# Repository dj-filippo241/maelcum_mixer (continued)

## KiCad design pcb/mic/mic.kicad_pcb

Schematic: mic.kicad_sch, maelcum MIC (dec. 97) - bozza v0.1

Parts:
C1, C2: 220u 35V; CP_Radial_D8.0mm_P3.50mm
C3: 47u 10V; CP_Radial_D5.0mm_P2.00mm
C4, C8: 10u 35V; CP_Radial_D5.0mm_P2.00mm
C5, C9: 47u 35V; CP_Radial_D6.3mm_P2.50mm
C6, C10: 470u 25V; CP_Radial_D8.0mm_P3.50mm
C7, C11: 100u 25V; CP_Radial_D6.3mm_P2.50mm
C12, C13: 1u 50V; C_1206_3216Metric
C14, C15, C39: 1u 25V; C_1206_3216Metric
C16, C17, C19, C20: 4u7 25V; C_1206_3216Metric
C18, C21: 10u 25V; C_1206_3216Metric
C22, C23: 100p C0G; C_0805_2012Metric
C24, C25, C26, C27, C33, C34, C35, C36, C37, C38, C40, C45, C46, C47, C48, C52, C53, C54, C56, C57, C58, C59, C62, C63, C64, C65, C66, C67: 100n; C_0805_2012Metric
C28, C29: 220n C0G; C_1210_3225Metric
C30: 22p C0G; C_0805_2012Metric
C31, C49: 47p C0G; C_0805_2012Metric
C32: 100n C0G; C_1206_3216Metric
C41, C42: 180n C0G; C_1206_3216Metric
C43, C44: 10n C0G; C_1206_3216Metric
C50, C51: 1u C0G; C_1206_3216Metric
C55: 220n C0G; C_1206_3216Metric
C60, C61: 10p C0G; C_0805_2012Metric
D1, D3, D5, D6, D7, D8, D9, D10, D11, D12, D13, D14, D15: 1N4148W; D_SOD-123
D2, D4: S1G; D_SMA
FB1, FB2, FB3, FB4, FB5, FB6, FB7: ferrite 600R; L_1206_3216Metric
H1, H2: CHASSIS; MountingHole_3.2mm_M3_Pad
J1: C96 maschio; DIN41612_C_3x32_Male_Horizontal_THT
J2: 2x12 cavo piatto; PinHeader_2x12_P2.54mm_Vertical
J3: XLR (cavo); PinHeader_1x03_P2.54mm_Vertical
Q1, Q2: 2N7002; SOT-23
Q40: BD139; TO-126-3_Vertical
Q41: BD140; TO-126-3_Vertical
R1, R4: 120 1%; R_0805_2012Metric
R2, R5: 1k74 1%; R_0805_2012Metric
R3, R6, R27, R37, R38, R58, R87: 1k; R_0805_2012Metric
R7, R8: 150k 0.1%; R_0805_2012Metric
R9, R11: 10 1%; R_0805_2012Metric
R10, R12: 47k 1%; R_0805_2012Metric
R13: 2k32 1%; R_0805_2012Metric
R14, R15: 499 0.1%; R_0805_2012Metric
R16: 32.4 0.1%; R_0805_2012Metric
R17, R18, R19, R20, R69, R71: 1k 0.1%; R_0805_2012Metric
R21: 8k45 0.1%; R_0805_2012Metric
R22: 16k9 0.1%; R_0805_2012Metric
R23: 332 0.1%; R_0805_2012Metric
R24: 5k36 0.1%; R_0805_2012Metric
R25, R43, R44, R53, R54, R56, R57, R62, R64, R65, R66, R89, R90, R91, R92, R93, R94, R95, R96: 10k 0.1%; R_0805_2012Metric
R26: 2k49 0.1%; R_0805_2012Metric
R28: 3M; R_0805_2012Metric
R29: 133k 0.1%; R_0805_2012Metric
R30: 7k68 0.1%; R_0805_2012Metric
R31: 6k65 0.1%; R_0805_2012Metric
R32: 1k1 0.1%; R_0805_2012Metric
R33, R34, R36, R67, R68, R86: 10k; R_0805_2012Metric
R35: 750k; R_0805_2012Metric
R39, R40: 324 0.1%; R_0805_2012Metric
R41: 4k75 0.1%; R_0805_2012Metric
R42: 2k26 0.1%; R_0805_2012Metric
R45, R46, R47: 49k9 0.1%; R_0805_2012Metric
R48, R52, R55, R76, R77, R78, R79, R80, R81: 20k 0.1%; R_0805_2012Metric
R49: 5k1; R_0805_2012Metric
R50: 150k; R_0805_2012Metric
R51: 51; R_0805_2012Metric
R59: 1M; R_0805_2012Metric
R60: 100; R_0805_2012Metric
R61: 16k 0.1%; R_0805_2012Metric
R63: 169k 0.1%; R_0805_2012Metric
R70: 2k 0.1%; R_0805_2012Metric
R72, R74: 4k99 0.1%; R_0805_2012Metric
R73, R75: 274 0.1%; R_0805_2012Metric
R82, R83, R84, R85: 2k2; R_0805_2012Metric
R88: 100k; R_0805_2012Metric
RV1: 50k; Potentiometer_Bourns_3266W_Vertical
U1, U2, U8, U11: OPA1612AIDR; SOIC-8_3.9x4.9mm_P1.27mm
U3, U4, U6, U7, U10: OPA1654AIDR; SOIC-14_3.9x8.7mm_P1.27mm
U5: V2181L; SOIC-8_3.9x4.9mm_P1.27mm
U9: ADG1434YRUZ; TSSOP-20_4.4x6.5mm_P0.65mm
U30: LM339DR; SOIC-14_3.9x8.7mm_P1.27mm
U40: LM317; TO-220-3_Vertical
U41: LM337; TO-220-3_Vertical
U42: 78L15; SOT-89-3
U43: 79L15; SOT-89-3
U44: LT3045EMSE; MSOP-12-1EP_3x4.039mm_P0.65mm_EP1.651x2.845mm
U45: LT3094EMSE; MSOP-12-1EP_3x4.039mm_P0.65mm_EP1.651x2.845mm

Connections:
+5V: FB5.1, J1.a21, J1.a22
+5VF: C3.1, C40.1, FB5.2, J2.20, R33.1, R35.1, R36.1, R86.1, R88.2, U30.3 (VCC)
+15LN: C18.1, C24.1, C26.1, C33.1, C47.1, C52.1, C56.1, C58.1, D5.1 (K), D7.1 (K), R29.1, R63.1, RV1.1, U1.8 (V+), U2.8 (V+), U3.4 (V+), U5.7 (V+), U6.4 (V+), U7.4 (V+), U11.8 (V+), U44.10 (OUTS), U44.11 (OUT), U44.12 (OUT)
+15SW: C14.1, C64.1, U9.16 (VDD), U42.1 (OUT)
+18V: C7.1, C17.1, C45.1, C62.1, C66.1, Q40.1 (E), U4.4 (V+), U8.8 (V+), U10.4 (V+), U44.1 (IN), U44.2 (IN), U44.3 (IN), U44.4 (EN/UV), U44.7 (PGFB)
-15LN: C21.2, C25.2, C27.2, C34.2, C48.2, C53.2, C57.2, C59.2, D6.2 (A), D8.2 (A), R49.2, RV1.3, U1.4 (V-), U2.4 (V-), U3.11 (V-), U6.11 (V-), U7.11 (V-), U11.4 (V-), U45.10 (OUTS), U45.11 (OUT), U45.12 (OUT)
-15SW: C15.2, C65.2, U9.5 (VSS), U43.3 (VO)
-18V: C11.2, C20.2, C46.2, C63.2, C67.2, Q41.1 (E), U4.11 (V-), U8.4 (V-), U10.11 (V-), U45.1 (IN), U45.2 (IN), U45.3 (EN/UV), U45.5 (PGFB), U45.13 (IN)
ADJ+: C4.1, D1.2 (A), R1.2, R2.1, U40.1 (ADJ)
ADJ-: C8.2, D3.1 (K), R4.2, R5.1, U41.1 (ADJ)
AGND: C1.2, C2.1, C4.2, C5.2, C6.2, C7.2, C8.1, C9.1, C10.1, C11.1, C12.2, C13.1, C14.2, C15.1, C16.2, C17.2, C18.2, C19.1, C20.1, C21.1, C24.2, C25.1, C26.2, C27.1, C32.2, C33.2, C34.1, C35.2, C36.2, C37.2, C45.2, C46.1, C47.2, C48.1, C50.2, C51.2, C52.2, C53.1, C54.2, C55.2, C56.2, C57.1, C58.2, C59.1, C62.2, C63.1, C64.2, C65.1, C66.2, C67.1, J1.a13, J1.a14, J1.a15, J1.a16, J1.a17, J1.a18, J1.a19, J1.a20, J1.b3, J1.b6, J1.b9, J1.b12, J1.b15, J1.b18, J1.b21, J1.b24, J1.b27, J1.b30, J2.1, J2.5, J2.9, J2.13, J2.19, R2.2, R5.2, R7.2, R8.2, R10.2, R12.2, R20.2, R22.2, R26.2, R28.2, R32.2, R42.2, R51.2, R59.2, R64.2, R68.2, R71.2, R73.2, R75.2, U2.5 (+), U3.5 (+), U4.3 (+), U4.10 (+), U4.12 (+), U5.2 (EC+), U5.6 (GND), U6.3 (+), U6.5 (+), U6.10 (+), U7.10 (+), U8.3 (+), U8.5 (+), U9.4 (S1B), U9.6 (GND), U9.7 (S2B), U9.14 (S3B), U9.17 (S4B), U11.5 (+), U42.2 (GND), U43.1 (GND), U44.6 (ILIM), U44.9 (GND), U44.13 (GND), U45.6 (ILIM), U45.9 (GND)
BASE+: C6.1, Q40.3 (B), R3.2
BASE-: C10.2, Q41.3 (B), R6.2
CF: C23.1, FB7.2, R11.1
CHASSIS: C22.2, C23.2, H1.1, H2.1, J1.a25, J1.a26, J3.1
CTRL_GND: C3.2, C38.2, C39.2, C40.2, J1.a23, J1.a24, J1.c16, J1.c20, J1.c24, J1.c28, J2.24, Q2.2 (S), R34.2, U30.12 (GND)
D1A: D9.2 (A), R27.2
DN: R17.2, R18.1, U2.2 (-)
DOUT: C31.1, R27.1, U3.8
DP: R19.2, R20.1, U2.3 (+)
DRV_L: C60.2, R77.2, R78.1, U8.1
DRV_R: C61.2, R80.2, R81.1, U8.7
DSUB: R62.2, R65.1, U7.7
ECF: R72.1, R73.1, U11.2 (-)
ECM: R74.2, R75.1, U5.3 (EC-)
ECO: R72.2, R74.1, U11.1
ECS: R69.2, R70.2, R71.1, U11.3 (+)
F1: R14.2, R16.1, U1.2 (-)
F2: R15.2, R16.2, U1.6 (-)
GFD: Q1.3 (D), R38.2
GINV: C30.1, J2.3, U3.6 (-)
GLOBAL_MUTE: J1.c9, R87.1
GP1: J2.2, R23.2
GP2: J2.4, R24.1
HF: C22.1, FB6.2, R9.1
HN: D15.2 (A), R65.2, R66.1, U7.9 (-)
HO: D14.2 (A), D15.1 (K), U7.8
HOLD: C31.2, C32.1, D9.1 (K), R28.1, U3.9 (-), U3.12 (+)
HP: R21.2, R23.1, U3.1, U3.2 (-)
HW: D11.2 (A), R54.2, R56.1
IC: D7.2 (A), D8.1 (K), R11.2, R12.1, R13.2, U1.5 (+)
IH: D5.2 (A), D6.1 (K), R9.2, R10.1, R13.1, U1.3 (+)
INJ1: R89.1, R90.1, U10.1, U10.2 (-)
INJ2: R91.1, R92.1, U10.6 (-), U10.7
INJ3: R93.1, R94.1, U10.8, U10.9 (-)
INJ4: R95.1, R96.1, U10.13 (-), U10.14
K1: C28.2, C29.1, R21.1
K2: C29.2, R22.1, U3.3 (+)
KG: Q1.2 (S), U30.13 (4OUT)
KR: D10.2 (A), R37.2, U30.14 (3OUT)
LIM: D14.1 (K), R66.2, R69.1
LKG: J2.21, R38.1
LKR: J2.22, R37.1
LQ: D10.1 (K), Q1.1 (G), R36.2, U30.2 (2OUT)
LT: C39.1, R35.2, U30.1 (1OUT), U30.5 (2IN+)
MET: U3.13 (-), U3.14, U30.6 (1IN-), U30.8 (3IN-), U30.10 (4IN-)
MG: R25.2, R26.1, U3.10 (+)
MRC: C55.1, R67.2, R68.1, U7.12 (+)
MSUM6_L: J1.b1, R78.2
MSUM6_R: J1.b2, R81.2
MUTE_CV: R70.1, U7.13 (-), U7.14
MUTE_G: Q2.1 (G), R87.2, R88.1
MUTE_SW: J2.23, R67.1
NA: C41.1, J2.6, R39.2
NB: C41.2, C42.1, J2.7, U4.2 (-)
NC: C42.2, J2.8, R40.1
NDR_L: C60.1, R76.2, R77.1, U8.2 (-)
NDR_R: C61.1, R79.2, R80.1, U8.6 (-)
NHA: C43.2, C44.1, R41.1
NHB: C44.2, R42.1, U4.5 (+)
NIV: C49.1, R52.1, U5.8 (OUT), U6.2 (-)
NSH: R45.2, R46.2, R47.1, U4.13 (-)
NU2: U2.6 (-), U2.7
NU11: U11.6 (-), U11.7
NVH: R43.2, R44.1, U4.9 (-)
O1: R14.1, R17.1, U1.1
O2: R15.1, R19.1, U1.7
PK: C50.1, R58.2, R59.1, R60.1
POST: C49.2, J2.14, R52.2, R53.1, R55.1, R76.1, R79.1, U6.1
POSTEQ: R47.2, R48.1, U4.14
PRE: C30.2, R24.2, R25.1, R39.1, U3.7
RAN: D12.1 (K), R53.2, R54.1, U6.6 (-)
RAO: D11.1 (K), D12.2 (A), U6.7
RAW+22: FB3.1, J1.a5, J1.a6
RAW+27: FB1.1, J1.a1, J1.a2
RAW-22: FB4.1, J1.a7, J1.a8
RAW-27: FB2.1, J1.a3, J1.a4
RBN: R55.2, R56.2, R57.1, U6.9 (-)
RECT: R57.2, U6.8, U6.12 (+)
S1: C28.1, R18.2, U2.1
S1_OUT_L: J1.b4, R89.2
S1_OUT_R: J1.b5, R90.2
S2_OUT_L: J1.b7, R91.2
S2_OUT_R: J1.b8, R92.2
S3_OUT_L: J1.b10, R93.2
S3_OUT_R: J1.b11, R94.2
S4_OUT_L: J1.b13, R95.2
S4_OUT_R: J1.b14, R96.2
SDK: D13.1 (K), R58.1, U6.13 (-)
SDO: D13.2 (A), U6.14
SETN: C19.2, R8.1, U45.8 (SET)
SETP: C16.1, R7.1, U44.8 (SET)
SIN1: R82.2, U9.2 (S1A), U9.3 (D1), U10.3 (+)
SIN2: R83.2, U9.8 (D2), U9.9 (S2A), U10.5 (+)
SIN3: R84.2, U9.12 (S3A), U9.13 (D3), U10.10 (+)
SIN4: R85.2, U9.18 (D4), U9.19 (S4A), U10.12 (+)
SM: C51.1, R60.2, U7.3 (+)
SMB: R61.1, U7.1, U7.2 (-)
SMUTE_N: Q2.3 (D), R86.2, U9.1 (IN1), U9.10 (IN2), U9.11 (IN3), U9.20 (IN4)
SUBN: R61.2, R62.1, U7.6 (-)
SUBP: C54.1, R63.2, R64.1, U7.5 (+)
SW1: J2.15, R82.1
SW2: J2.16, R83.1
SW3: J2.17, R84.1
SW4: J2.18, R85.1
SWSYM: R50.1, RV1.2
SYM: R50.2, R51.1, U5.4 (SYM)
V22F+: C12.1, FB3.2, U42.3 (IN)
V22F-: C13.2, FB4.2, U43.2 (VI)
V27F+: C1.1, D2.1 (K), FB1.2, U40.3 (VI)
V27F-: C2.2, D4.2 (A), FB2.2, U41.2 (VI)
VEE: R49.1, U5.5 (V-)
VG: C37.1, R31.2, R32.1, U30.11 (4IN+)
VHN: J2.10, R44.2, U4.8
VHP: J2.12, R41.2, R43.1, U4.6 (-), U4.7
VIN: R48.2, U5.1 (IN)
VLO: C43.1, R40.2, R45.1, U4.1
VR: C35.1, R29.2, R30.1, U30.7 (1IN+)
VREG+: C5.1, D1.1 (K), D2.2 (A), Q40.2 (C), R1.1, R3.1, U40.2 (VO)
VREG-: C9.2, D3.2 (A), D4.1 (K), Q41.2 (C), R4.1, R6.1, U41.3 (VO)
VTL: C38.1, R33.2, R34.1, U30.4 (2IN-)
VY: C36.1, R30.2, R31.1, U30.9 (3IN+)
WPH: J2.11, R46.1
XCOLD: FB7.1, J3.3
XHOT: FB6.1, J3.2

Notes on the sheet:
BACKPLANE C96 (classe MIC/GEN, MSUM6)
ALIM: +18V (LM317 + BD139)
ALIM: -18V (LM337 + BD140)
ALIM: +15SW (78L15)
ALIM: -15SW (79L15)
ALIM: +5VF
ALIM: +15LN (LT3045)
ALIM: -15LN (LT3094)
INGRESSO XLR: RFI, clamp, carico 2,32k, bias 2x47k (mic-pre.inc)
INA +30,05 dB e differenziale unity (OPA1612)
PASSA-ALTO 60 Hz, STADIO 2 (0...+30 dB), DETECTOR del LED (OPA1654)
LED tricolore (LM339)
EQ2 (+-18)
VCA del MUTE e del limiter (dec. 111, 145; sim/mic/mic-limiter.cir)
DRIVER MSUM6 L/R (invertenti, todo 227)
MANDATE S1-S4 (pot sul cavo, mute globale, iniezione)
CAVO SCHEDA COMANDI (J2)

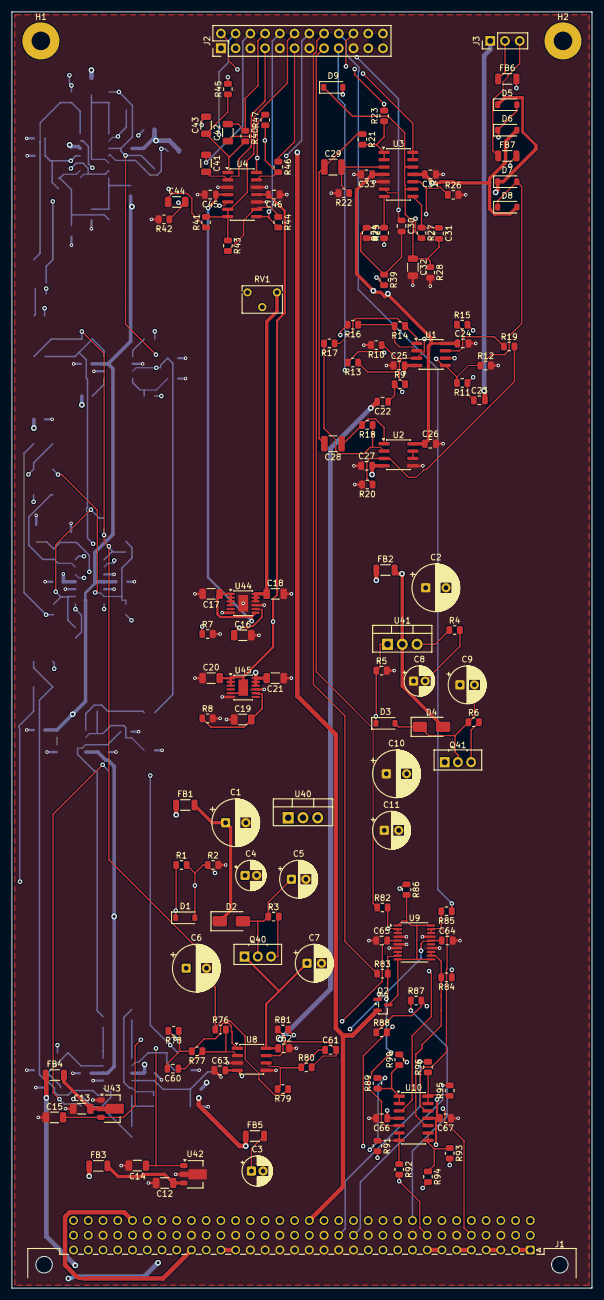
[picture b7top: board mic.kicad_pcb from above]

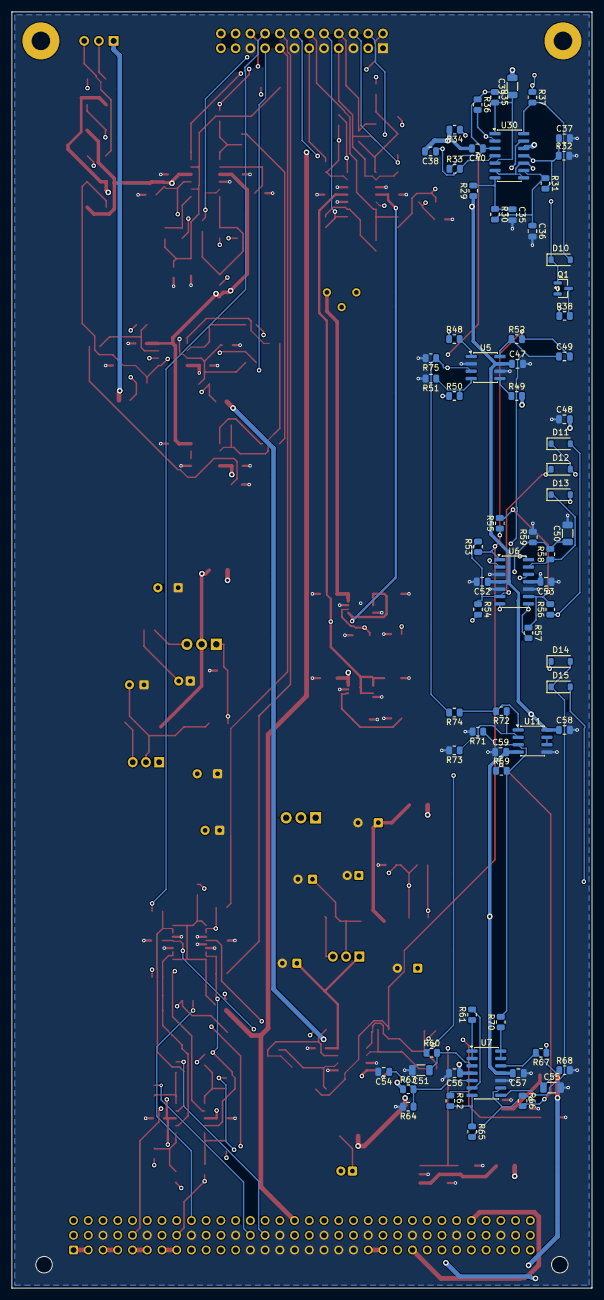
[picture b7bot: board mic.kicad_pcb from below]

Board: 4 copper layers, 100.0 x 220.0 mm, 213 parts (69 on the bottom side), 135 nets.

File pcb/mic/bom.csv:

quantita;valore;impronta;riferimenti;nota
2;220u 35V;CP_Radial_D8.0mm_P3.50mm;C1 C2;
2;1u 50V;C_1206_3216Metric;C12 C13;
3;1u 25V;C_1206_3216Metric;C14 C15 C39;
1;4u7 25V;C_1206_3216Metric;C16;rumore del riferimento (datasheet: 4,7 uF)
3;4u7 25V;C_1206_3216Metric;C17 C19 C20;
2;10u 25V;C_1206_3216Metric;C18 C21;
2;100p C0G;C_0805_2012Metric;C22 C23;RFI verso il telaio
28;100n;C_0805_2012Metric;C24 C25 C26 C27 C33 C34 C35 C36 C37 C38 C40 C45 C46 C47 C48 C52 C53 C54 C56 C57 C58 C59 C62 C63 C64 C65 C66 C67;
2;220n C0G;C_1210_3225Metric;C28 C29;
1;47u 10V;CP_Radial_D5.0mm_P2.00mm;C3;
1;22p C0G;C_0805_2012Metric;C30;
2;47p C0G;C_0805_2012Metric;C31 C49;
1;100n C0G;C_1206_3216Metric;C32;hold: niente altro sul nodo (sim/meter)
2;10u 35V;CP_Radial_D5.0mm_P2.00mm;C4 C8;
2;180n C0G;C_1206_3216Metric;C41 C42;
2;10n C0G;C_1206_3216Metric;C43 C44;
2;47u 35V;CP_Radial_D6.3mm_P2.50mm;C5 C9;
1;1u C0G;C_1206_3216Metric;C50;Ch: C0G o film
1;1u C0G;C_1206_3216Metric;C51;Cs: lisciatura 0,1 ms
1;220n C0G;C_1206_3216Metric;C55;rampa 1,1 ms (dec. 111)
2;470u 25V;CP_Radial_D8.0mm_P3.50mm;C6 C10;
2;10p C0G;C_0805_2012Metric;C60 C61;NOTA: Cf come i ricevitori a massa virtuale
2;100u 25V;CP_Radial_D6.3mm_P2.50mm;C7 C11;
1;1N4148W;D_SOD-123;D1;scarica Cadj
1;1N4148W;D_SOD-123;D10;rosso acceso durante il latch
1;1N4148W;D_SOD-123;D13;diodo del superdiodo
1;S1G;D_SMA;D2;protezione inversa
8;1N4148W;D_SOD-123;D3 D6 D8 D9 D11 D12 D14 D15;
1;S1G;D_SMA;D4;
2;1N4148W;D_SOD-123;D5 D7;NOTA: clamp 1N4148W al posto del BAV199 (pinout non verificato)
7;ferrite 600R;L_1206_3216Metric;FB1 FB2 FB3 FB4 FB5 FB6 FB7;
1;C96 maschio;DIN41612_C_3x32_Male_Horizontal_THT;J1;DIN 41612 C 3x32, angolo retto
1;2x12 cavo piatto;PinHeader_2x12_P2.54mm_Vertical;J2;cavo piatto corto (<= 10 cm) verso la scheda comandi dietro il pannello (dec. 133)
1;XLR (cavo);PinHeader_1x03_P2.54mm_Vertical;J3;NOTA: cavo verso l'XLR femmina; pin 1 a CHASSIS al connettore (grounding §4)
1;2N7002;SOT-23;Q1;spegne il verde durante il latch del rosso
1;2N7002;SOT-23;Q2;GLOBAL_MUTE alto = muto
1;BD139;TO-126-3_Vertical;Q40;
1;BD140;TO-126-3_Vertical;Q41;
2;120 1%;R_0805_2012Metric;R1 R4;
2;47k 1%;R_0805_2012Metric;R10 R12;bias di modo comune (CMRR 74 dB)
1;2k32 1%;R_0805_2012Metric;R13;Zin differenziale 2,26 kOhm
2;499 0.1%;R_0805_2012Metric;R14 R15;
1;32.4 0.1%;R_0805_2012Metric;R16;Rg: G1 = 1 + 998/32,4 = 31,8
1;1k 0.1%;R_0805_2012Metric;R17;caldo sull'ingresso -: il differenziale inverte (todo 227)
3;1k 0.1%;R_0805_2012Metric;R18 R19 R20;
1;1k74 1%;R_0805_2012Metric;R2;E96 1,74k = 19,4 V (fx-send NOTE punto 16)
1;8k45 0.1%;R_0805_2012Metric;R21;
1;16k9 0.1%;R_0805_2012Metric;R22;R_fb = R_gnd/2: Butterworth
1;332 0.1%;R_0805_2012Metric;R23;
1;5k36 0.1%;R_0805_2012Metric;R24;
17;10k 0.1%;R_0805_2012Metric;R25 R43 R44 R53 R54 R56 R57 R64 R65 R89 R90 R91 R92 R93 R94 R95 R96;
1;2k49 0.1%;R_0805_2012Metric;R26;
1;3M;R_0805_2012Metric;R28;release 0,3 s (dec. 81)
1;133k 0.1%;R_0805_2012Metric;R29;
1;1k;R_0805_2012Metric;R3;NOTA: cap-moltiplicatore come il FX-SEND (~50 mA)
1;7k68 0.1%;R_0805_2012Metric;R30;
1;6k65 0.1%;R_0805_2012Metric;R31;
1;1k1 0.1%;R_0805_2012Metric;R32;
4;10k;R_0805_2012Metric;R33 R34 R36 R68;
1;750k;R_0805_2012Metric;R35;latch del rosso: 0,69 x 750k x 1u = 0,52 s
1;1k;R_0805_2012Metric;R37;~2,8 mA nel rosso (LED alta efficienza, metering §1)
1;1k;R_0805_2012Metric;R38;~2,8 mA nel verde
2;324 0.1%;R_0805_2012Metric;R39 R40;
1;4k75 0.1%;R_0805_2012Metric;R41;NOTA: mic-mono §5.1 dice 4,7k/2,25k (~5 kHz); backend.inc 5,23k/2,5k
1;2k26 0.1%;R_0805_2012Metric;R42;E96 di 2,25k
3;49k9 0.1%;R_0805_2012Metric;R45 R46 R47;
7;20k 0.1%;R_0805_2012Metric;R48 R52 R55 R76 R77 R79 R80;
1;5k1;R_0805_2012Metric;R49;valore del datasheet a -15 V (master: 6,19k a -18 V)
1;1k74 1%;R_0805_2012Metric;R5;
1;150k;R_0805_2012Metric;R50;
1;51;R_0805_2012Metric;R51;
1;1k;R_0805_2012Metric;R58;attacco 1 ms
1;1M;R_0805_2012Metric;R59;rilascio 1 s (variante 2)
3;1k;R_0805_2012Metric;R6 R27 R87;
1;100;R_0805_2012Metric;R60;
1;16k 0.1%;R_0805_2012Metric;R61;NOTA: inseguitore su SM, così il sottrattore non carica Ch
1;10k 0.1%;R_0805_2012Metric;R62;G = 10k/16k = 0,625
1;169k 0.1%;R_0805_2012Metric;R63;SUBP = 0,838 V = VTH x 10/26: VTH 2,179 V
1;10k 0.1%;R_0805_2012Metric;R66;Rf: a riposo LIM a massa virtuale (11k con Ra)
1;10k;R_0805_2012Metric;R67;NOTA: tasto a ritenuta fra +5VF e MUTE_SW, come il MONO del master
1;1k 0.1%;R_0805_2012Metric;R69;Ra
2;150k 0.1%;R_0805_2012Metric;R7 R8;
1;2k 0.1%;R_0805_2012Metric;R70;Rb: MUTE 2,5 V -> +0,79 V sulla rete; al pin 0,77 V = -126 dB
1;1k 0.1%;R_0805_2012Metric;R71;Rc
1;4k99 0.1%;R_0805_2012Metric;R72;stadio del limite x19,21 (todo 288)
2;274 0.1%;R_0805_2012Metric;R73 R75;
1;4k99 0.1%;R_0805_2012Metric;R74;partitore 1/19,21: op-amp al rail = 0,80 V al pin
2;20k 0.1%;R_0805_2012Metric;R78 R81;R di somma lato sorgente (dec. 97)
4;2k2;R_0805_2012Metric;R82 R83 R84 R85;
1;10k;R_0805_2012Metric;R86;IN alto = suona (VIH 2,0 V)
1;100k;R_0805_2012Metric;R88;senza master il modulo resta muto (fail-safe, fx-send NOTE 5)
2;10 1%;R_0805_2012Metric;R9 R11;limita la corrente dei clamp
1;50k;Potentiometer_Bourns_3266W_Vertical;RV1;trim di simmetria (vca-trim §3.1)
1;OPA1612AIDR;SOIC-8_3.9x4.9mm_P1.27mm;U1;coppia INA
1;OPA1654AIDR;SOIC-14_3.9x8.7mm_P1.27mm;U10;buffer d'iniezione, non invertenti
1;OPA1612AIDR;SOIC-8_3.9x4.9mm_P1.27mm;U11;stadio del limite del pin EC- (todo 288); seconda sezione libera, inseguitore a massa
1;OPA1612AIDR;SOIC-8_3.9x4.9mm_P1.27mm;U2;differenziale; seconda sezione libera, inseguitore a massa
1;OPA1654AIDR;SOIC-14_3.9x8.7mm_P1.27mm;U3;passa-alto, stadio 2 (pot GAIN 5k sul cavo: GP1-GINV-GP2), superdiodo e buffer del LED
1;LM339DR;SOIC-14_3.9x8.7mm_P1.27mm;U30;NOTA: GND a CTRL_GND (correnti dei LED fuori da AGND); ingressi riferiti ad AGND
1;OPA1654AIDR;SOIC-14_3.9x8.7mm_P1.27mm;U4;EQ2: LOW, HIGH follower, HIGH invertente, HIGH somma
1;LM317;TO-220-3_Vertical;U40;
1;LM337;TO-220-3_Vertical;U41;
1;78L15;SOT-89-3;U42;
1;79L15;SOT-89-3;U43;
1;LT3045EMSE;MSOP-12-1EP_3x4.039mm_P0.65mm_EP1.651x2.845mm;U44;EN/UV a IN; ILIM a massa; PG libero; PGFB a IN (come master-segnale.py)
1;LT3094EMSE;MSOP-12-1EP_3x4.039mm_P0.65mm_EP1.651x2.845mm;U45;EN/UV a IN; PG libero; PGFB a IN; ILIM a massa; VIOC libero
1;V2181L;SOIC-8_3.9x4.9mm_P1.27mm;U5;
1;OPA1654AIDR;SOIC-14_3.9x8.7mm_P1.27mm;U6;I/V del VCA, raddrizzatore A e B, superdiodo
1;OPA1654AIDR;SOIC-14_3.9x8.7mm_P1.27mm;U7;inseguitore di SM, sottrattore, mezza onda, inseguitore del MUTE
1;OPA1612AIDR;SOIC-8_3.9x4.9mm_P1.27mm;U8;driver MSUM invertenti (F2)
1;ADG1434YRUZ;TSSOP-20_4.4x6.5mm_P0.65mm;U9;mute globale delle mandate (dec. 94b): D e SxA sul nodo, SxB a massa

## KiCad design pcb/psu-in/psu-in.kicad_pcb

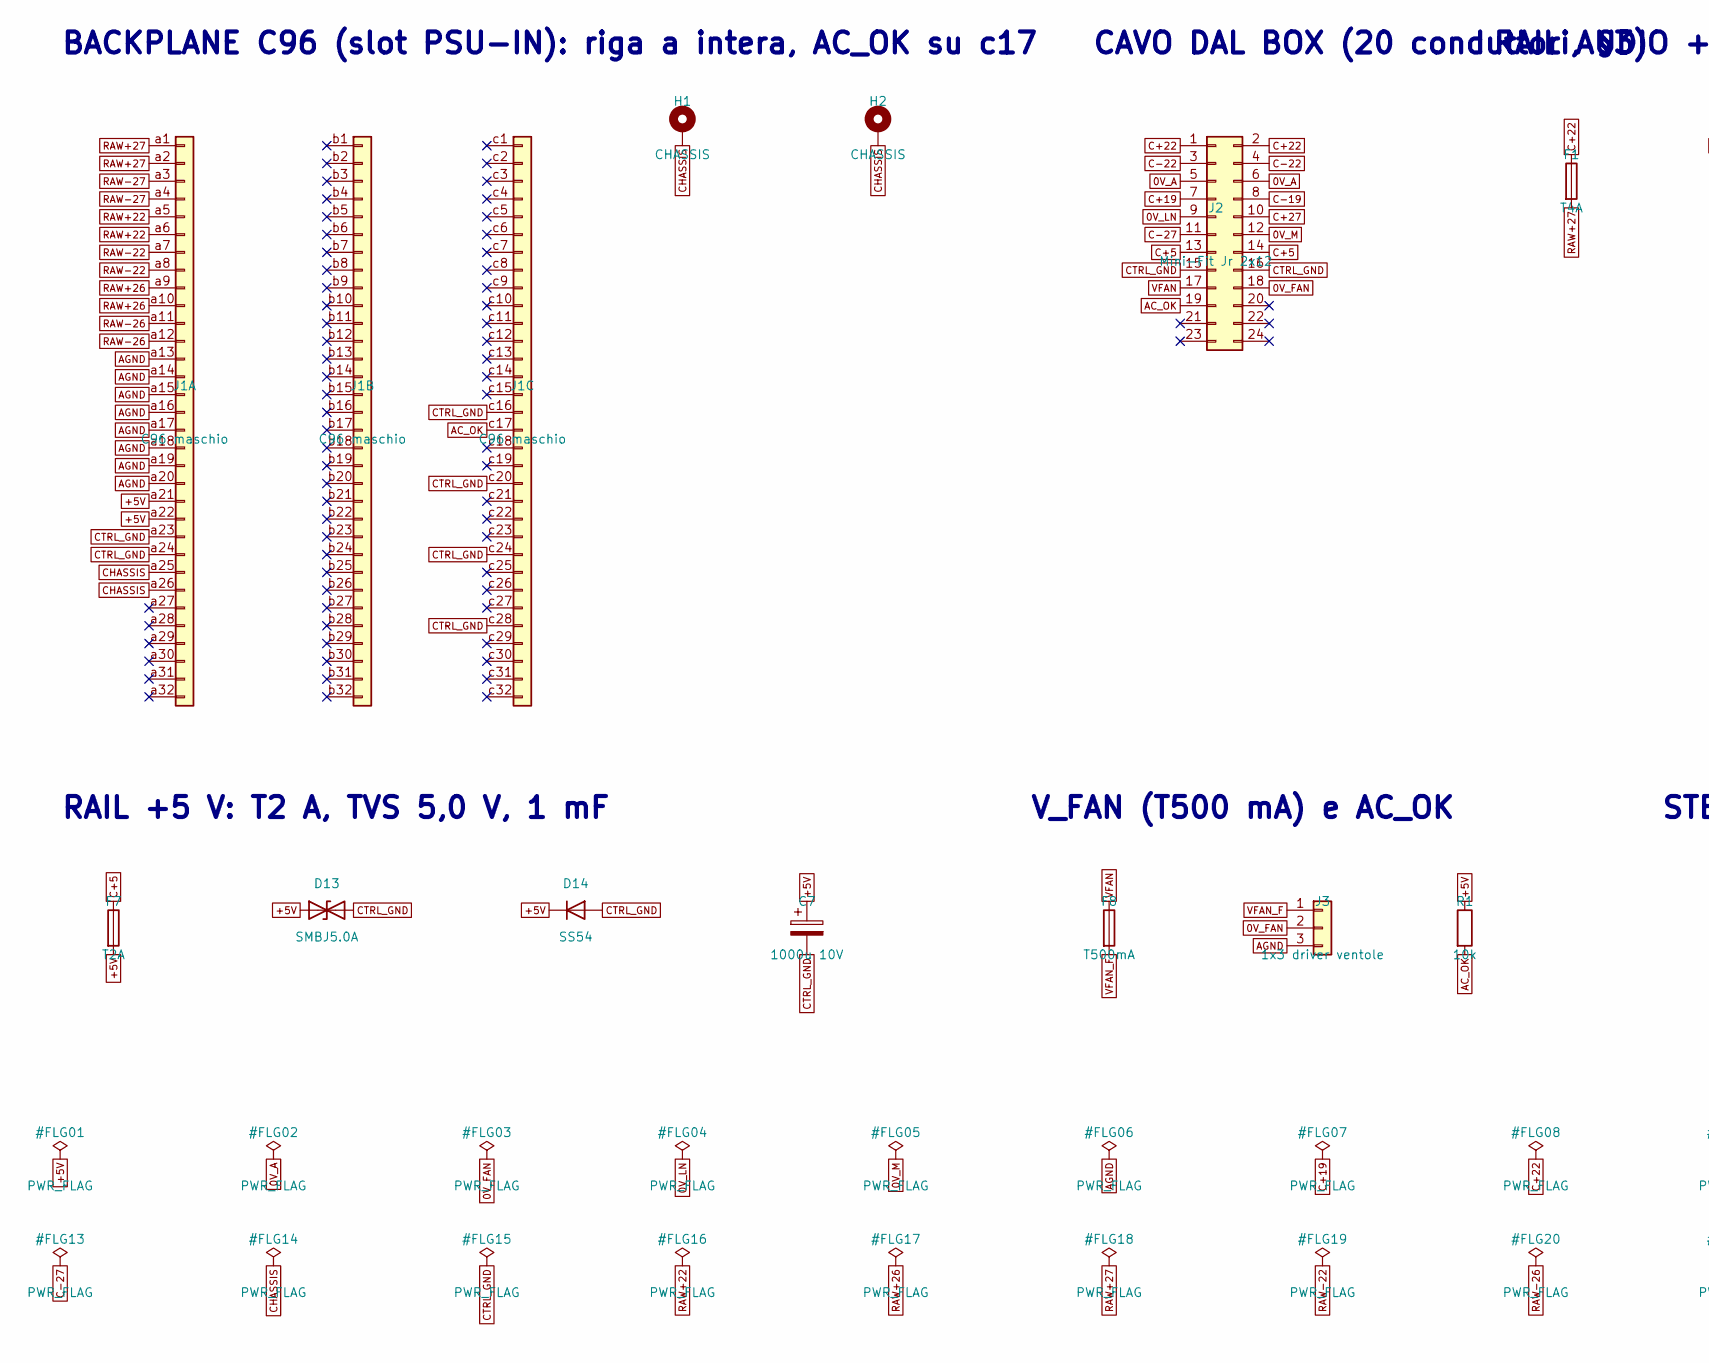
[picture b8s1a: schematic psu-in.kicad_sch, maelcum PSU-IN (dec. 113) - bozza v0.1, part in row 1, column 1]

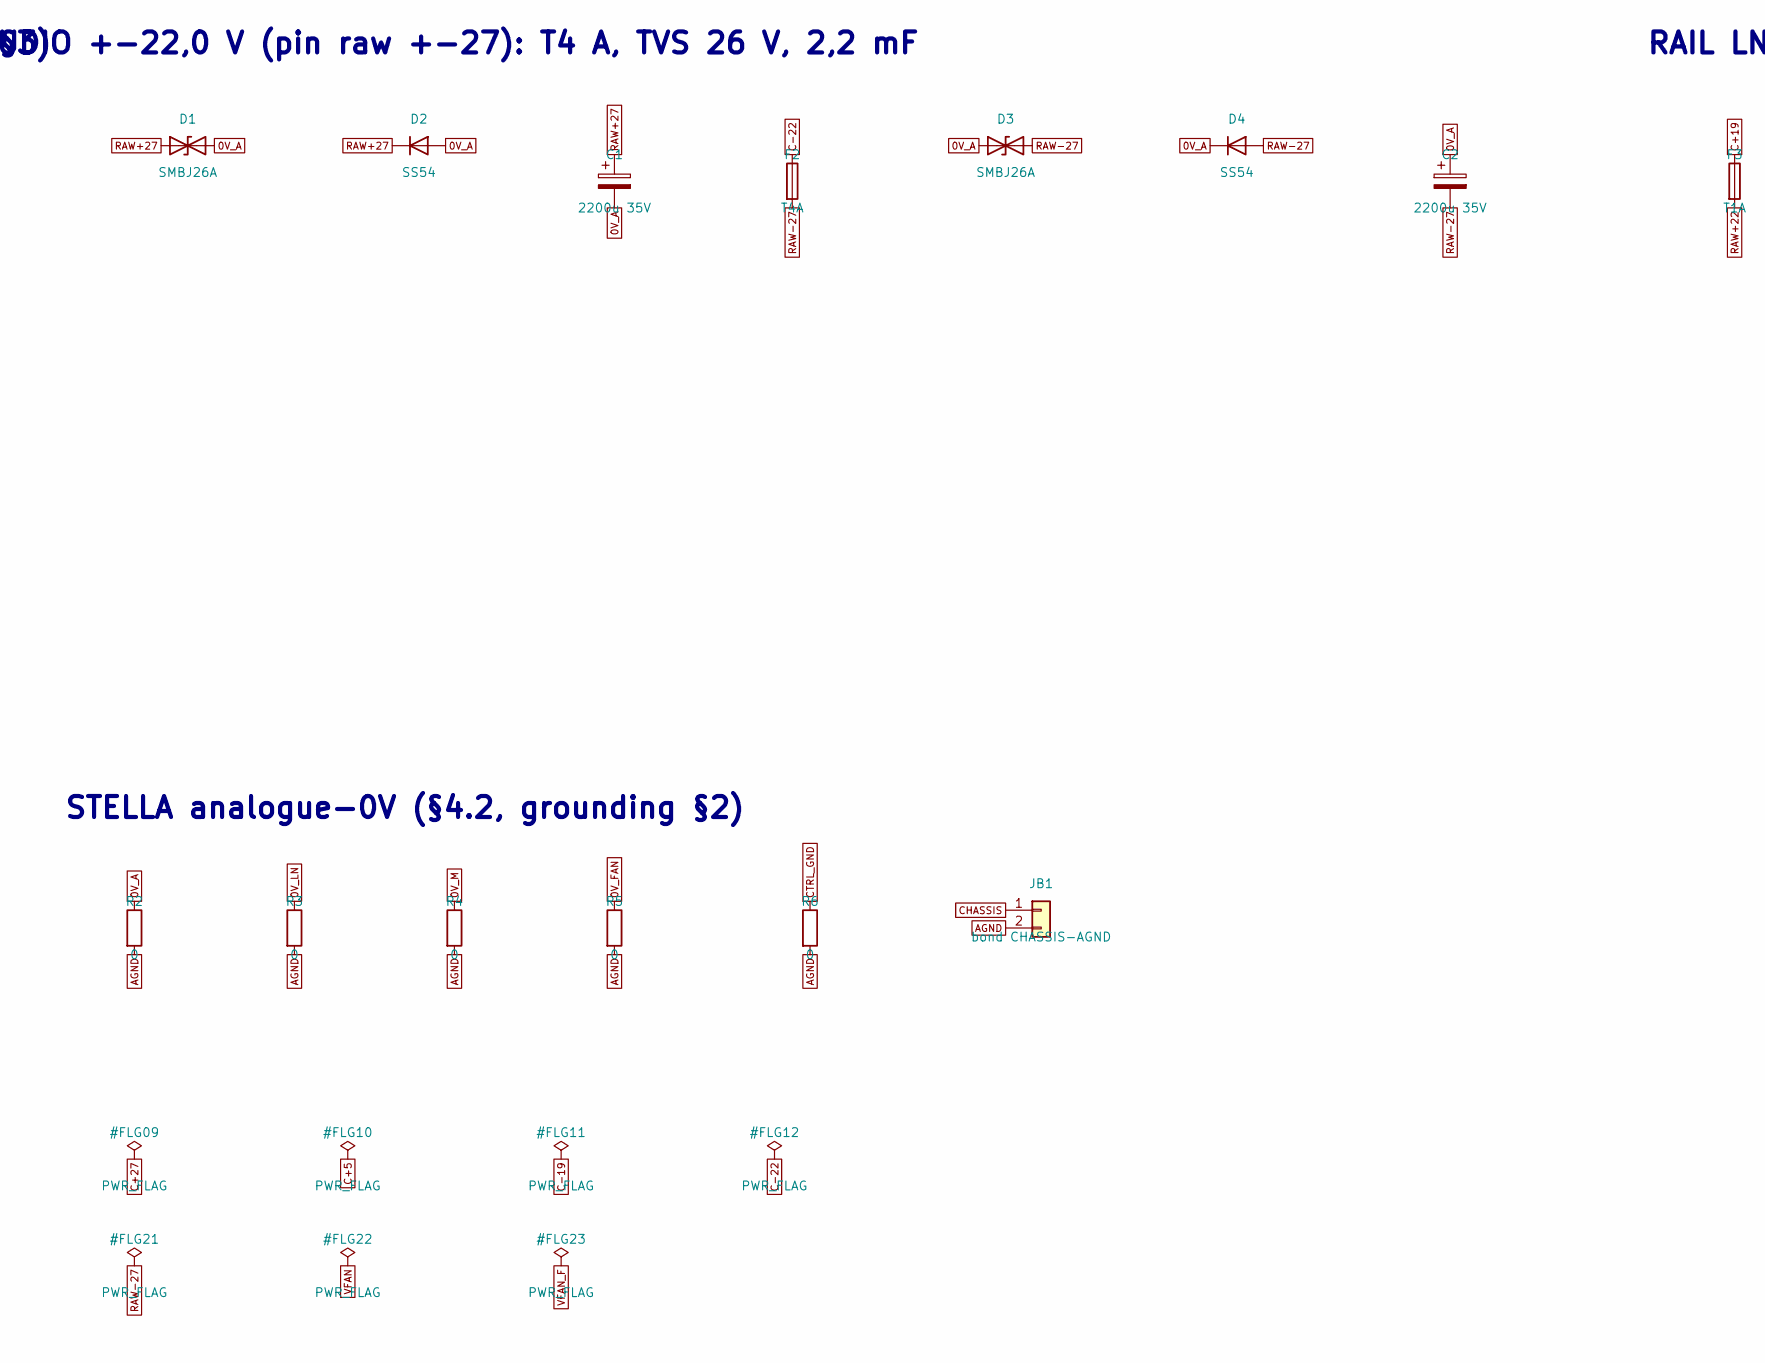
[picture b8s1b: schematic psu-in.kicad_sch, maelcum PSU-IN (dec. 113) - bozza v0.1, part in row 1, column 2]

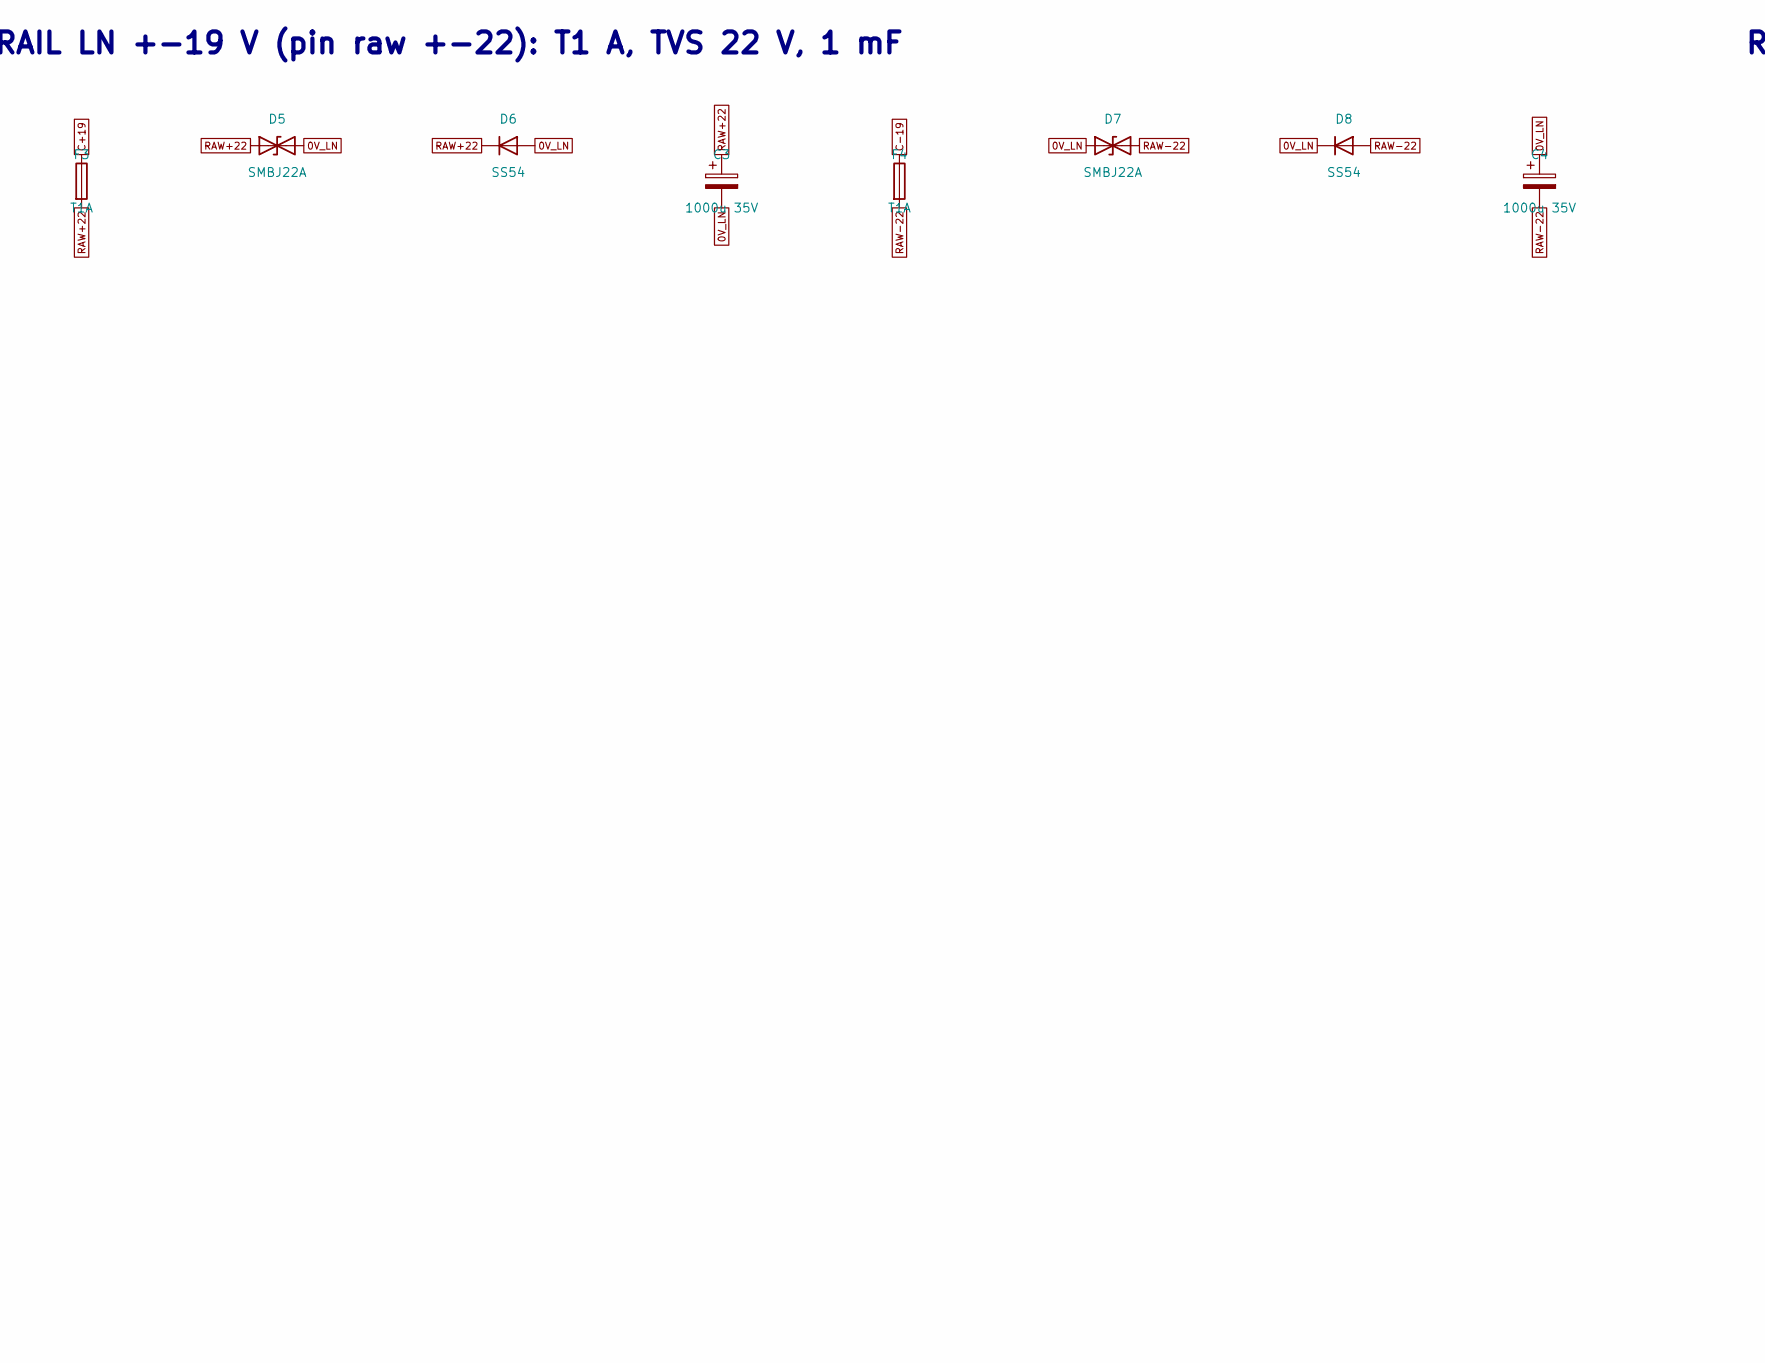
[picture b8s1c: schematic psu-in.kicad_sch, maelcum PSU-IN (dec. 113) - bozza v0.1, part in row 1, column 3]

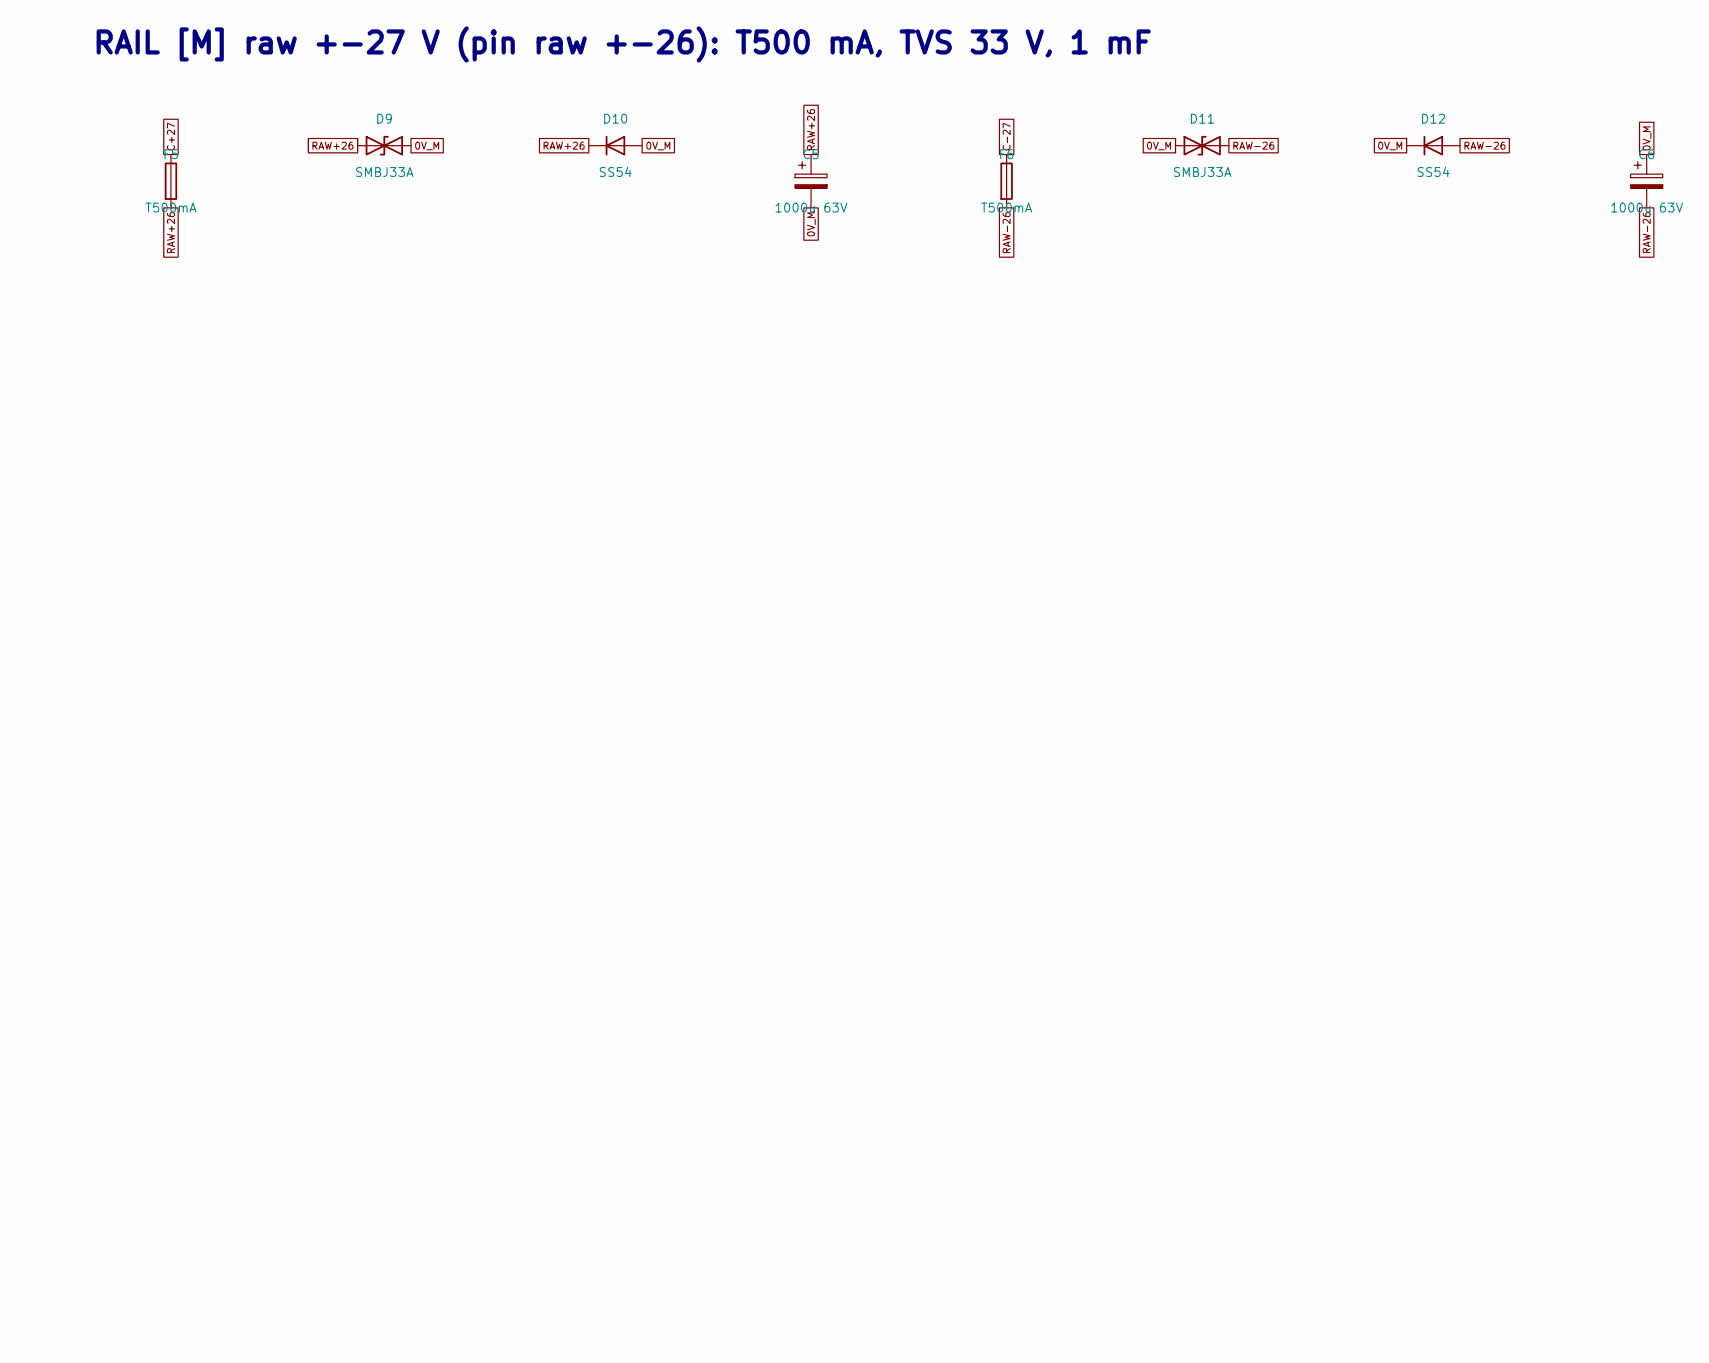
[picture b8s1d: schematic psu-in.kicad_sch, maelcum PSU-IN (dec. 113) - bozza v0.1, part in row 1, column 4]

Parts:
C1, C2: 2200u 35V; CP_Radial_D18.0mm_P7.50mm
C3, C4: 1000u 35V; CP_Radial_D12.5mm_P5.00mm
C5, C6: 1000u 63V; CP_Radial_D12.5mm_P5.00mm
C7: 1000u 10V; CP_Radial_D12.5mm_P5.00mm
D1, D3: SMBJ26A; D_SMB
D2, D4, D6, D8, D10, D12, D14: SS54; D_SMC
D5, D7: SMBJ22A; D_SMB
D9, D11: SMBJ33A; D_SMB
D13: SMBJ5.0A; D_SMB
F1, F2: T4A; Fuseholder_Cylinder-5x20mm_Stelvio-Kontek_PTF78_Horizontal_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
F3, F4: T1A; Fuseholder_Cylinder-5x20mm_Stelvio-Kontek_PTF78_Horizontal_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
F5, F6, F8: T500mA; Fuseholder_Cylinder-5x20mm_Stelvio-Kontek_PTF78_Horizontal_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
F7: T2A; Fuseholder_Cylinder-5x20mm_Stelvio-Kontek_PTF78_Horizontal_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
H1, H2: CHASSIS; MountingHole_3.2mm_M3_Pad
J1: C96 maschio; DIN41612_C_3x32_Male_Horizontal_THT
J2: Mini-Fit Jr 2x12; Molex_Mini-Fit_Jr_5566-24A2_2x12_P4.20mm_Vertical
J3: 1x3 driver ventole; PinHeader_1x03_P2.54mm_Vertical
JB1: bond CHASSIS-AGND; PinHeader_1x02_P2.54mm_Vertical
R1: 10k; R_0805_2012Metric
R2, R3, R4, R5, R6: 0; R_2512_6332Metric

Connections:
0V_A: C1.2, C2.1, D1.2 (A2), D2.2 (A), D3.1 (A1), D4.1 (K), J2.5, J2.6, R2.1
0V_FAN: J2.18, J3.2, R5.1
0V_LN: C3.2, C4.1, D5.2 (A2), D6.2 (A), D7.1 (A1), D8.1 (K), J2.9, R3.1
0V_M: C5.2, C6.1, D9.2 (A2), D10.2 (A), D11.1 (A1), D12.1 (K), J2.12, R4.1
+5V: C7.1, D13.1 (A1), D14.1 (K), F7.2, J1.a21, J1.a22, R1.1
AC_OK: J1.c17, J2.19, R1.2
AGND: J1.a13, J1.a14, J1.a15, J1.a16, J1.a17, J1.a18, J1.a19, J1.a20, J3.3, JB1.2, R2.2, R3.2, R4.2, R5.2, R6.2
C+5: F7.1, J2.13, J2.14
C+19: F3.1, J2.7
C+22: F1.1, J2.1, J2.2
C+27: F5.1, J2.10
C-19: F4.1, J2.8
C-22: F2.1, J2.3, J2.4
C-27: F6.1, J2.11
CHASSIS: H1.1, H2.1, J1.a25, J1.a26, JB1.1
CTRL_GND: C7.2, D13.2 (A2), D14.2 (A), J1.a23, J1.a24, J1.c16, J1.c20, J1.c24, J1.c28, J2.15, J2.16, R6.1
RAW+22: C3.1, D5.1 (A1), D6.1 (K), F3.2, J1.a5, J1.a6
RAW+26: C5.1, D9.1 (A1), D10.1 (K), F5.2, J1.a9, J1.a10
RAW+27: C1.1, D1.1 (A1), D2.1 (K), F1.2, J1.a1, J1.a2
RAW-22: C4.2, D7.2 (A2), D8.2 (A), F4.2, J1.a7, J1.a8
RAW-26: C6.2, D11.2 (A2), D12.2 (A), F6.2, J1.a11, J1.a12
RAW-27: C2.2, D3.2 (A2), D4.2 (A), F2.2, J1.a3, J1.a4
VFAN: F8.1, J2.17
VFAN_F: F8.2, J3.1

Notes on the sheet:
BACKPLANE C96 (slot PSU-IN): riga a intera, AC_OK su c17
CAVO DAL BOX (20 conduttori, §3)
RAIL AUDIO +-22,0 V (pin raw +-27): T4 A, TVS 26 V, 2,2 mF
RAIL LN +-19 V (pin raw +-22): T1 A, TVS 22 V, 1 mF
RAIL [M] raw +-27 V (pin raw +-26): T500 mA, TVS 33 V, 1 mF
RAIL +5 V: T2 A, TVS 5,0 V, 1 mF
V_FAN (T500 mA) e AC_OK
STELLA analogue-0V (§4.2, grounding §2)

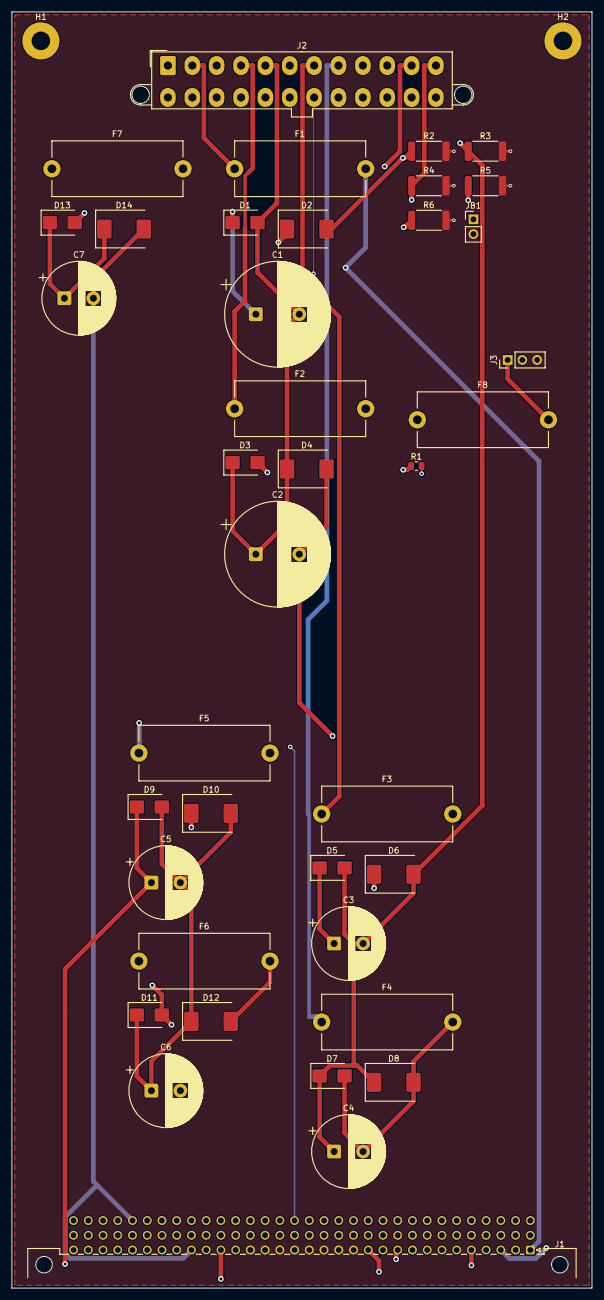
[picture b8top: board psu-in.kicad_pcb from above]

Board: 4 copper layers, 100.0 x 220.0 mm, 41 parts (0 on the bottom side), 24 nets.
